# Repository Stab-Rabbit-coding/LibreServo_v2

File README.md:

# 

An Open source controller to convert any servo motor to the best smart servo.

This fork is focused improving the LibreServo design by moving to an TI MSPM0G3518-Q1 MCU, which provides simultaneous CAN-FD and RS485, and a robust cryptographic suite, along with an SLB9672 TPM.

**Version 4.0.0.** Upstream LibreServo shipped v2.3.1 and had a v3 in mind. The changes in this fork — new MCU family, TPM, CAN-FD alongside RS-485, an isolated transceiver pair, and a hardware security stack — go past what that v3 was scoped to be, so this fork takes the next major number rather than a v3.x that would collide with it.

**EDA tooling:** this fork has moved to **KiCad**. Autodesk EAGLE is end-of-life and no longer supported, so all new schematic and layout work is done in KiCad 9 under [`PCB/kicad/`](PCB/kicad/) as `LibreServo-v4.0.0`. The upstream EAGLE `.sch`/`.brd` files are kept in [`PCB/`](PCB/) for backward compatibility and design history; they stay frozen at v2.3.1 and are not renumbered. See [`PCB/ReadMe.md`](PCB/ReadMe.md).

This project was born as a necessity of mine to build a biped robot with intelligent servos to be able to “feel the muscles” to walk more human like. In the past we had OpenServo, and I think this project inherits something from it, but OpenServo died many years ago and it didn't reach my expectations anyway (power, communications...), and the commercial alternatives are way too expensive (Dynamixel, Herkulex, Lynxmotion...).

My goal with LibreServo is to make any standard servo the “smartest” one in the market. The "gold standard" nowadays is Robotis-Dynamixel, LibreServo should be better than that, that’s my goal at least.

A few characteristics of LibreServo:

    Compatible with standard servo motors (No need to change the bottom cover of them!)
    Voltage: From 4.5V up to 18V (Recommended: 5-14V)
    Communications: Isolated RS-485 and CAN-FD. Max Speed 9Mbps. Daisy chained. CRC-16
    Amp: Up to 16A continuous (WSD3069DN56) (Version >2.3)
    Micro-Controller (this fork): TI MSPM0G3518-Q1 (cortex-M0+@80MHz, 256KB flash, 128KB SRAM, CAN-FD + 5 UART, AES-256 with CMAC/GCM, key store, CSC secure boot). Upstream uses an STM32F301k8 (cortex-M4@72MHz).
    Trusted Platform Module: SLB9672
    Position sensor: Magnetic encoder, 16 bits of resolution! 360 degrees (AEAT-8800). Using the servo motor potentiometer will be possible to lower the cost but will lost precision and some characteristics.
    For the encoder I have designed 3D parts to substitute the potentiometer and used the same hole/space than the original.
    LibreServo will generate their own curves (sine ramps, trapezoidal ramps, hermitian curves...)
    Current sensor: +-15A ACS711
Communication Protocol: <a href="https://www.libreservo.com/en/articulo/libreservo-commands-part-one">LibreServo Commands</a><BR>

More info in <a href="https://www.libreservo.com/en">LibreServo</a>.

<p align="center">
</p>

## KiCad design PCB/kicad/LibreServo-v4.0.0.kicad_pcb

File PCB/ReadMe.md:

# LibreServo v4.0.0 — PCB

**This fork is at version 4.0.0.** Upstream LibreServo shipped v2.3.1 and had a v3 in
mind; the changes made here — new MCU family, CAN-FD alongside RS-485, an isolated
transceiver pair, and a hardware security stack — go past what that v3 was scoped to be,
so the fork takes the next major number rather than a v3.x that would collide with it.

**KiCad is the primary EDA tool for this fork.** Autodesk EAGLE is end-of-life and no
longer supported, so all new schematic and layout work happens in KiCad. The EAGLE
artefacts are retained for backward compatibility with upstream LibreServo and as
design history; they are frozen at the v2.3.1 they were forked from and are not
renumbered or updated.

## Layout of this directory

| Path | Version | Tool | Status |
| --- | --- | --- | --- |
| [`kicad/`](kicad/) | 4.0.0 | KiCad 9.0.2 | **Primary — edit here** |
| `LibreServo-v2.3.1.sch` / `.brd` | 2.3.1 | EAGLE 7.6.0 | Frozen, backward compatibility |
| [`old/`](old/) | 2, 2.1, 2.2 | EAGLE 7.6.0 | Frozen, superseded upstream revisions |
| [`Gerbers/`](Gerbers/) | 2.3.1 | — | Production output, EAGLE-era |
| [`datasheets/`](datasheets/) | — | — | Local copies of vendor documents |

`kicad/LibreServo-v4.0.0.kicad_sch` and `.kicad_pcb` were produced by KiCad 9.0.2's
EAGLE importer from the frozen `.sch`/`.brd`, then carried forward independently. Both
carry `rev 4.0.0` in their title block. The Gerbers have **not** been regenerated at
4.0.0 and must not be fabricated as if they had been.

### Reading the imported symbol library

The importer names symbols after the **EAGLE symbol**, not the EAGLE deviceset, so
`kicad/LibreServo-v4.0.0-eagle-import.kicad_sym` does not always agree with the part
number. Most notably `U1` uses the symbol `MSPM0G3519` while the fitted part is a
**MSPM0G3518-Q1** (`M0G3518QRHBRQ1`). Look parts up by reference designator, not by
value.

### Known import defect: `#U1`, `#U5`, `#U6`

The three parts that had no package in the EAGLE library — `U1` (MSPM0G3518-Q1), `U5`
(ADM2587E) and `U6` (ADM3055E) — imported as `#`-prefixed pseudo-components, the class
KiCad reserves for power flags. They are consequently **absent from the exported
netlist** and are not yet real board parts. Fixing this is the first layout task; see
[`MSPM0G3518-MCU-swap.md`](MSPM0G3518-MCU-swap.md) §6.2.

## Design-change records

Each MCU / interface upgrade pass has its own decision record. Superseded records are
kept with a banner rather than deleted.

- [`MSPM0G3518-MCU-swap.md`](MSPM0G3518-MCU-swap.md) — **current**: `U1` is a TI
  MSPM0G3518-Q1 in VQFN-32 (RHB).
- [`MSPM0G3507-MCU-swap.md`](MSPM0G3507-MCU-swap.md) — superseded.
- [`S32K144-MCU-swap.md`](S32K144-MCU-swap.md) — superseded.
- [`RS485-CANFD-TPM-upgrade.md`](RS485-CANFD-TPM-upgrade.md) — superseded.

Records written on or before 2026-08-03 state that EAGLE is the project standard and
that the final product must be delivered in EAGLE, and refer to the design as v2.3.1.
**Neither is true** as of 2026-08-04; where such a record and this file disagree, this
file governs.

## Bill of materials

`LibreServo-v2.3_BOM.txt` is the EAGLE-era BOM and is several MCU generations stale.
It still lists `U1` as an `STM32F301K8U6` and predates `ADM2587E` / `ADM3055E`. It
needs regeneration from the KiCad schematic, which cannot happen until the `#U1` /
`#U5` / `#U6` defect above is fixed.

## Attribution

Upstream board design © LibreServo, CC BY-SA 4.0 — see
[LibreServo](https://www.libreservo.com/en). This fork's modifications follow the same
licence. This file was rewritten by **Claude Opus 5** (Anthropic) on 2026-08-04 at the
direction of the human maintainer, who set both the EAGLE-to-KiCad policy and the
4.0.0 version number; the original upstream text described the `.sch`/`.brd` pair and
mislabelled it as KiCad.

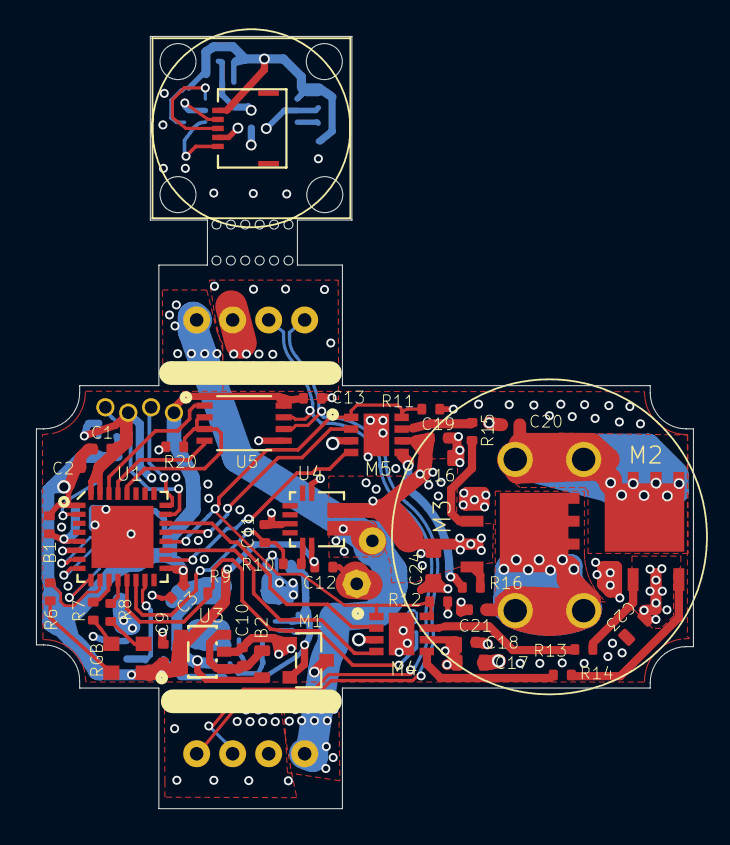
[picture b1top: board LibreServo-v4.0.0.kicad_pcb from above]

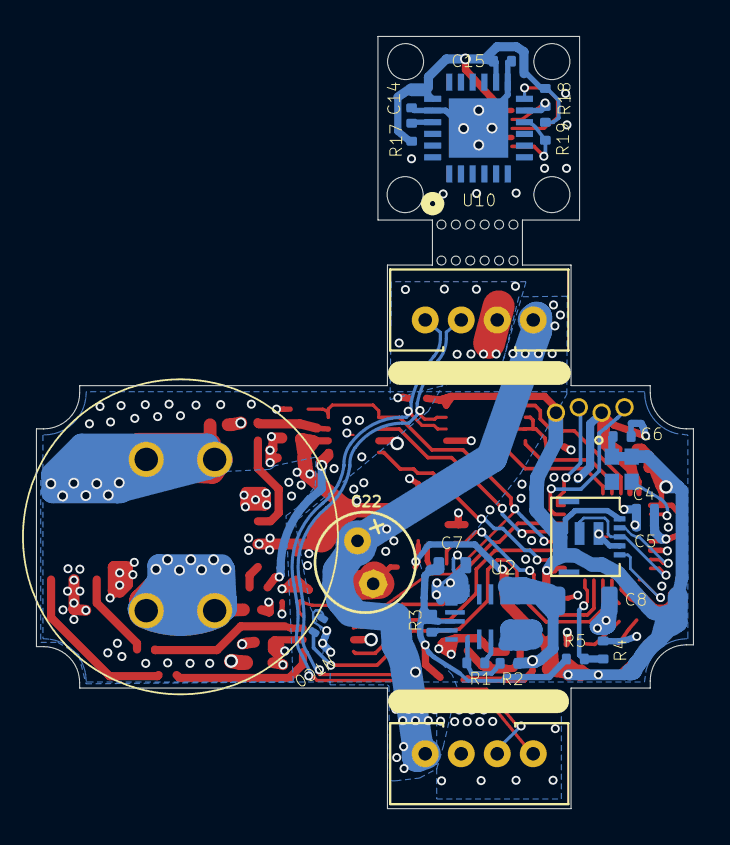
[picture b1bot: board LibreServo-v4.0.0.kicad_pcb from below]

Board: 6 copper layers, 36.5 x 42.9 mm, 84 parts (23 on the bottom side), 54 nets.

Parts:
B1: 0402
B2: 0603
C1: 4.7u; 0402
C2, C3, C5, C6, C11, C14, C18, C19: 100n; 0402
C4, C9, C10, C12, C13, C15: 1u; 0402
C7, C16, C17, C23, C24: 10u; 0603
C8: 22u; 1206
C20, C21: 10n; 0402
C22: 220uF; E2,5-6_MIN
M1: M1; SOT23
M2, M3: MOSFET_N+P; DFN5X6
M4, M5: FAN3227/4; MLP8
NTC0: 0402_MIN
R1: 12.5K; 0402
R2: 47K; 0402
R3: 150K; 0402
R4, R9, R11, R12, R17, R18, R19, R20: 10K; 0402
R5: 51K; 0402
R6: 187; 0402
R7: 270; 0402
R8: 309; 0402
R10: 1.1k; 0402
R13, R14, R15, R16: 6; 0402
RGB0: LED_RGB_PLCC4_2.2X2; PLCC-4_2.2X2
U1: STM32F301/2; QFN32
U2: MPM3610; MPM36XX
U3: AP2112; SOT25
U4: ACS711; ACS711-QFN
U5: SIT3485; MSOP-8
U10: AEAT-8800; QFN24
U$1, U$2: SLOT; SERVO_SLOT
U$3, U$4: FFC-5; FFC-5-0.5
U$5: HEADER_4_1.27_0.3
U$6: POTEN_SERVO
U$8, U$9: JST_PH-4_HOLEB; JST_PH-4_HOLE_B
U$100: OSCILATOR; OSC-2X1.6
UNK_HOLE_0: dummyfp0
UNK_HOLE_1: dummyfp1
UNK_HOLE_2: dummyfp2
UNK_HOLE_3: dummyfp3
UNK_HOLE_4: dummyfp4
UNK_HOLE_5: dummyfp5
UNK_HOLE_6: dummyfp6
UNK_HOLE_7: dummyfp7
UNK_HOLE_8: dummyfp8
UNK_HOLE_9: dummyfp9
UNK_HOLE_10: dummyfp10
UNK_HOLE_11: dummyfp11
UNK_HOLE_12: dummyfp12
UNK_HOLE_13: dummyfp13
UNK_HOLE_14: dummyfp14
UNK_HOLE_15: dummyfp15

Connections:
711_OUT: R10.2, U4.P$11
+3V3: B1.2, C1.2, C2.2, C3.1, C6.1, C9.1, C12.2, C13.2, R9.2, RGB0.P$1, U1.1, U1.17, U3.5, U4.P$12, U5.P$8, U$4.P$5, U$5.P$1, U$6.P$1, U$100.P$1, U$100.P$4
+3V3_2: C14.1, C15.1, R17.2, R18.1, R19.1, U10.P$14, U10.P$19, U$3.P$1
+7V: C22.+, M1.P$2, U4.P$1, U$8.P$1, U$9.P$1
CLK-8MHZ: U1.2, U$100.P$3
EN-Q: M4.P$1, M4.P$8, M5.P$1, M5.P$8, R11.1, R12.1, U1.20
GND: C1.1, C2.1, C3.2, C4.2, C5.2, C6.2, C7.2, C8.1, C9.2, C10.2, C11.2, C12.1, C13.1, C16.1, C17.1, C18.1, C19.1, C20.2, C21.2, C22.-, C23.2, C24.2, M1.P$1, M2.P$1, M3.P$1, M4.P$3, M4.P$9, M5.P$3, M5.P$9, NTC0.1, R4.1, R11.2, R12.2, R20.2, U1.6, U1.16, U1.31, U1.32, U1.EP, U2.P$12, U2.P$13, U2.P$14, U3.2, U4.P$5, U4.P$7, U4.P$8, U4.P$9, U4.P$10, U5.P$5, U$4.P$2, U$5.P$3, U$6.P$3, U$8.P$2, U$9.P$2, U$100.P$2
GND_2: C14.2, C15.2, U10.P$13, U10.P$20, U10.P$25, U$3.P$4
IN_AP2112: B2.1, C10.1, U3.1, U3.3
LED_BLUE: R8.1, U1.12
LED_GREEN: R7.1, U1.11
LED_RED: R6.1, U1.10
M1-OUT: C7.1, M1.P$3, R3.2, R5.2, U2.P$16
M2-OUT: C20.1, M2.P$5, M2.P$6, M2.P$7, M2.P$8, M2.P$9, U$1.P$1
M3-OUT: C21.1, M3.P$5, M3.P$6, M3.P$7, M3.P$8, M3.P$9, U$2.P$1
M4-OUTA: M4.P$7, R13.2
M4-OUTA-IN: M2.P$2, R13.1
M4-OUTB: M4.P$5, R14.2
M4-OUTB-IN: M2.P$4, R14.1
M5-OUTA: M5.P$7, R15.2
M5-OUTA-IN: M3.P$2, R15.1
M5-OUTB: M5.P$5, R16.2
M5-OUTB-IN: M3.P$4, R16.1
MPM3610_AGND: R1.1, U2.P$3
MPM3610_EN: R3.1, U2.P$17
MPM3610_FB: R1.2, R2.1, U2.P$1
MPM3610_SW: U2.P$4, U2.P$5, U2.P$6
unnamed: R6.2, RGB0.P$4
unnamed: R7.2, RGB0.P$3
unnamed: R8.2, RGB0.P$2
unnamed: R17.1, U10.P$21
OUT_MPM3610: B2.2, C8.2, R2.2, U2.P$7, U2.P$8, U2.P$9
PWM-1: M5.P$4, U1.18
PWM-2: M5.P$2, U1.21
PWM-3: M4.P$4, U1.19
PWM-4: M4.P$2, U1.22
RS485_N: U5.P$7, U$8.P$3, U$9.P$3
RS485_P: U5.P$6, U$8.P$4, U$9.P$4
SEL_SERIAL: R20.1, U1.28, U5.P$2, U5.P$3
SPI_CLK: U1.9, U$4.P$1
SPI_CLK_2: R19.2, U10.P$10, U$3.P$5
SPI_IN: U1.7, U$4.P$4
SPI_IN_2: R18.2, U10.P$11, U$3.P$2
SPI_OUT: U1.8, U$4.P$3, U$6.P$2
SPI_OUT_2: U10.P$12, U$3.P$3
SWCLK: U1.24, U$5.P$2
SWDIO: U1.23, U$5.P$4
USART1_RX: U1.30, U5.P$1
USART1_TX: U1.29, U5.P$4
VDDA-FILTRADO: B1.1, C4.1, C5.1, U1.5
VMOT: C16.2, C17.2, C18.2, C19.2, C23.1, C24.1, M2.P$3, M3.P$3, M4.P$6, M5.P$6, U4.P$3
V_BAT: R4.2, R5.1, U1.15
V_CORRIENTE: C11.1, R10.1, U1.14
V_TEMP: NTC0.2, R9.1, U1.13

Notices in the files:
PCB/kicad/LibreServo-v4.0.0.kicad_pcb:
Fork of LibreServo v2.3.1 (CC BY-SA 4.0), https://www.libreservo.com/en
